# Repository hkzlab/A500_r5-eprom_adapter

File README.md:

# A500/A2000 EPROM Adapter

## Introduction

In this repository You'll find two no-frills boards that I designed with a simple problem to solve: allow me to install **multiple Kickstarts** in my Amiga 500 rev.5 units without having to shell out money for an expensive 27C400 that I then need to rewire to make compatible.

The board includes sockets for pullup resistors that are oftentimes required (if your Amiga doesn't already have them) when fitting an new EPROM.

The board accepts **two** 27C020/040/080 EPROMs programmed with concatenated Kickstart images.

## EPROMs Configuration

The Amiga 500 uses a 16-bit bus to access the Kickstart, as such, the original ROM and its replacements must be 16-bit memories: expensive and annoying to program.

This board merges the data path of two 8-bit EPROMs (cheaper, easier to program) to rebuild the 16-bit data path.

One must take care to divide the original Kickstart dumps in two halves by separating the most significant byte of each Word into a file, and the least significant into another.

See the following example. The following is a partial hex dump of Kickstart 1.3 for A500:

Once we split its words in High and Low bytes we'll get the following dump for the High part:

And the following for the Low part:

The **High** part will have to be inserted in the slot marked as **H** and the **Low** part in the slot marked as **L**.

You can use the [srecord](http://srecord.sourceforge.net/) tool to split the files:

```sh
srec_cat -o LOW.bin -binary fullrom.bin -binary -split 2 0
srec_cat -o HIGH.bin -binary fullrom.bin -binary -split 2 1

```

### A500 rev.5 configuration

The Amiga 500 rev.5 uses a non-standard pinout in its Kickstart socket: A17 line is connected to PIN 31, while it is normally on PIN 1 of the ROM chip.

You can wire the adapter to use this pinout by **bridging pins 2-3 of the J4 header**. If pins 1-2 are bridged, the A17 line goes to PIN 1.

### EPROM slots

Depending on which type of EPROM you use, you can fit a different number of Kickstart images in them.

- 27C020: 1 kickstart slot
- 27C040: 2 kickstarts slots (selectable with the A18 jumper)
- 27C080: 4 kickstarts slot (selectable by combining the A18 and A19 jumpers)

A18 and A19 are pulled-up through 4.7k resistors.

Every slot can host a 512kb Kickstart. If you wish to put a 256kb Kickstart in the slot, concatenate it with a copy of itself (stay on the safe side!).

To create an image to burn on the EPROMs I suggest following this procedure:

1. Take the required Kickstarts
2. Double the size of every 256kb Kickstart by concatenating it with a copy of itself
3. Concatenate the desired Kickstart dumps
4. Split the resulting binary file in high and low halves
5. Burn the halves to their respective EPROMs

The result will be like this for a 27C040:

```text
              HIGH EPROM     LOW  EPROM
         / .--------------.--------------.
        |  | 256k Kick A  | 256k Kick A  |
SLOT 1 <   +--------------+--------------+
        |  | 256k Kick A  | 256k Kick A  |
         \ +--------------+--------------+
         / |              |              |
        |  |     512k     |     512k     |
SLOT 2 <   |    Kick B    |    Kick B    |
        |  |              |              |
         \ '--------------'--------------'
```

## Board Variants

You'll find two variants of the same board in this repository. One uses DIP32 EPROMs, the other PLCC32.

PLCC32 version is a bit harder to solder, but is more compact.

**Install RN1 and RN2 only if your Amiga lacks pull-up resistors on the data lines**. Also, the **R1 and R2 resistors are to be installed ONLY if you fit a 9-resistor bussed network (so, 10 pin and not 11) or if you did not fit a resistor network at all** on RN1 and RN2. 11 pin bussed arrays are a bit hard to come by, so you can fit a 10 pin one and install two discrete resistors to make up for the missing ones.

### DIP32 Variant

#### BOM

- C1, C2: 100nF ceramic capacitors
- J2, J3: 1x2 2.54mm PCB headers
- J4: 1x3 2.54mm PCB header
- U2, U3: DIP32 sockets
- U1: install 2x20pin 2.54mm headers on the underside. **Find thin ones that can fit into sockets**.
- RN1, RN2: either 11 or 10pin 4.7k ohm bussed resistor networks.
  - If you fit a 10pin ones (9 resistor + common pin), leave the last pin empty and fit R1 and R2.
  - If you fit 11pin ones (10 resistors + common pin), leave R1 and R2 empty
- R1, R2: 4.7k ohm resistors. Read point above to see if you must install them or not.
- 2x 27C020/040/080 EPROMs, DIP32

### SMD PLCC32 variant

#### BOM

- C1, C2: 100nF ceramic capacitors
- J2, J3: 1x2 2.54mm PCB headers
- J4: 1x3 2.54mm PCB header
- U2, U3: PLCC32 SMD sockets
- U1: install 2x20pin 2.54mm headers on the underside. **Find thin ones that can fit into sockets**.
- RN1, RN2: either 11 or 10pin 4.7k ohm bussed resistor networks.
  - If you fit a 10pin ones (9 resistor + common pin), leave the last pin empty and fit R1 and R2.
  - If you fit 11pin ones (10 resistors + common pin), leave R1 and R2 empty
- R1, R2: 4.7k ohm resistors. Read point above to see if you must install them or not.
- 2x 27C020/040/080 EPROMs, DIP32

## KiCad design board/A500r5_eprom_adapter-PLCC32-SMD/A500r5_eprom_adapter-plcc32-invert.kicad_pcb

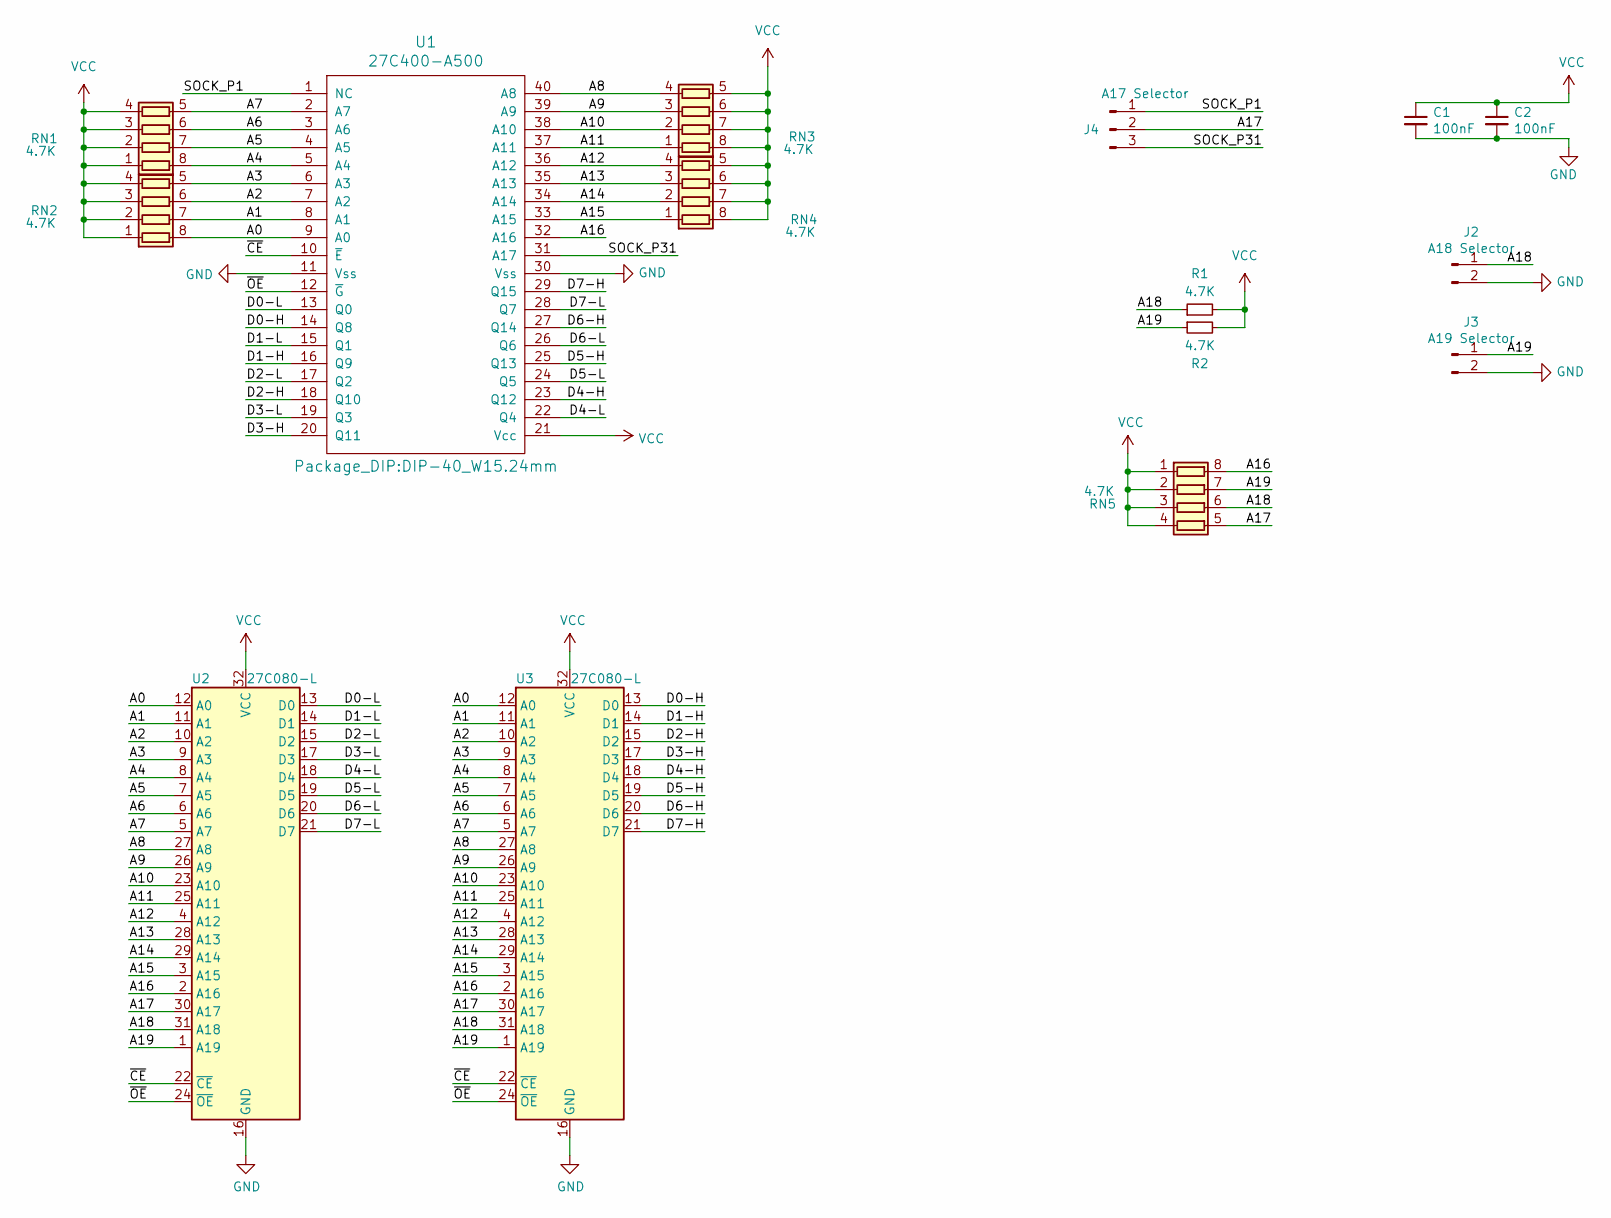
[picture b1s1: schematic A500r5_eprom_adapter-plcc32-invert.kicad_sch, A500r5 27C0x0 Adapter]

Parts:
C1, C2: 100nF; C_0603_1608Metric_Pad1.08x0.95mm_HandSolder
J2: A18 Selector; SolderJumper-2_P1.3mm_Open_RoundedPad1.0x1.5mm
J3: A19 Selector; SolderJumper-2_P1.3mm_Open_RoundedPad1.0x1.5mm
J4: A17 Selector; SolderJumper-3_P1.3mm_Open_RoundedPad1.0x1.5mm
R1, R2: 4.7K; R_0603_1608Metric_Pad0.98x0.95mm_HandSolder
RN1, RN2, RN3, RN4, RN5: 4.7K; R_Array_Convex_4x0612
U1: 27C400-A500; DIP-40_W15.24mm
U2, U3: 27C080-L; PLCC-32_11.4x14.0mm_P1.27mm

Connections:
/A0: RN2.8 (R1.2), U1.9 (A0), U2.12 (A0), U3.12 (A0)
/A1: RN2.7 (R2.2), U1.8 (A1), U2.11 (A1), U3.11 (A1)
/A2: RN2.6 (R3.2), U1.7 (A2), U2.10 (A2), U3.10 (A2)
/A3: RN2.5 (R4.2), U1.6 (A3), U2.9 (A3), U3.9 (A3)
/A4: RN1.8 (R1.2), U1.5 (A4), U2.8 (A4), U3.8 (A4)
/A5: RN1.7 (R2.2), U1.4 (A5), U2.7 (A5), U3.7 (A5)
/A6: RN1.6 (R3.2), U1.3 (A6), U2.6 (A6), U3.6 (A6)
/A7: RN1.5 (R4.2), U1.2 (A7), U2.5 (A7), U3.5 (A7)
/A8: RN3.4 (R4.1), U1.40 (A8), U2.27 (A8), U3.27 (A8)
/A9: RN3.3 (R3.1), U1.39 (A9), U2.26 (A9), U3.26 (A9)
/A10: RN3.2 (R2.1), U1.38 (A10), U2.23 (A10), U3.23 (A10)
/A11: RN3.1 (R1.1), U1.37 (A11), U2.25 (A11), U3.25 (A11)
/A12: RN4.4 (R4.1), U1.36 (A12), U2.4 (A12), U3.4 (A12)
/A13: RN4.3 (R3.1), U1.35 (A13), U2.28 (A13), U3.28 (A13)
/A14: RN4.2 (R2.1), U1.34 (A14), U2.29 (A14), U3.29 (A14)
/A15: RN4.1 (R1.1), U1.33 (A15), U2.3 (A15), U3.3 (A15)
/A16: RN5.8 (R1.2), U1.32 (A16), U2.2 (A16), U3.2 (A16)
/A17: J4.2, RN5.5 (R4.2), U2.30 (A17), U3.30 (A17)
/A18: J2.1, R1.1, RN5.6 (R3.2), U2.31 (A18), U3.31 (A18)
/A19: J3.1, R2.1, RN5.7 (R2.2), U2.1 (A19), U3.1 (A19)
/D0-H: U1.14 (Q8), U3.13 (D0)
/D0-L: U1.13 (Q0), U2.13 (D0)
/D1-H: U1.16 (Q9), U3.14 (D1)
/D1-L: U1.15 (Q1), U2.14 (D1)
/D2-H: U1.18 (Q10), U3.15 (D2)
/D2-L: U1.17 (Q2), U2.15 (D2)
/D3-H: U1.20 (Q11), U3.17 (D3)
/D3-L: U1.19 (Q3), U2.17 (D3)
/D4-H: U1.23 (Q12), U3.18 (D4)
/D4-L: U1.22 (Q4), U2.18 (D4)
/D5-H: U1.25 (Q13), U3.19 (D5)
/D5-L: U1.24 (Q5), U2.19 (D5)
/D6-H: U1.27 (Q14), U3.20 (D6)
/D6-L: U1.26 (Q6), U2.20 (D6)
/D7-H: U1.29 (Q15), U3.21 (D7)
/D7-L: U1.28 (Q7), U2.21 (D7)
/SOCK_P1: J4.1, U1.1 (NC)
/SOCK_P31: J4.3, U1.31 (A17)
/~CE: U1.10 (~E), U2.22 (~CE), U3.22 (~CE)
/~OE: U1.12 (~G), U2.24 (~OE), U3.24 (~OE)
GND: C1.2, C2.2, J2.2, J3.2, U1.11 (Vss), U1.30 (Vss), U2.16 (GND), U3.16 (GND)
VCC: C1.1, C2.1, R1.2, R2.2, RN1.1 (R1.1), RN1.2 (R2.1), RN1.3 (R3.1), RN1.4 (R4.1), RN2.1 (R1.1), RN2.2 (R2.1), RN2.3 (R3.1), RN2.4 (R4.1), RN3.5 (R4.2), RN3.6 (R3.2), RN3.7 (R2.2), RN3.8 (R1.2), RN4.5 (R4.2), RN4.6 (R3.2), RN4.7 (R2.2), RN4.8 (R1.2), RN5.1 (R1.1), RN5.2 (R2.1), RN5.3 (R3.1), RN5.4 (R4.1), U1.21 (Vcc), U2.32 (VCC), U3.32 (VCC)

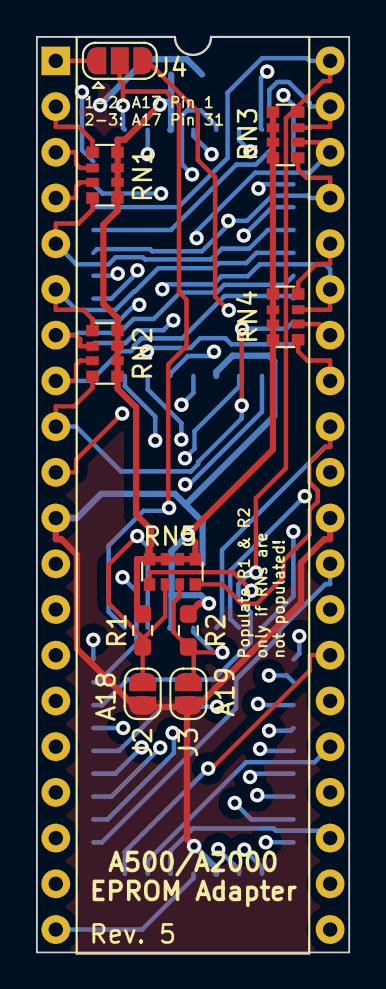
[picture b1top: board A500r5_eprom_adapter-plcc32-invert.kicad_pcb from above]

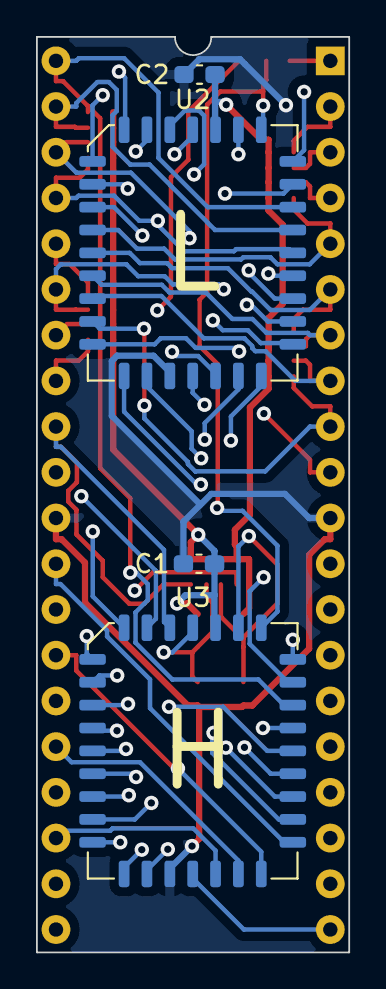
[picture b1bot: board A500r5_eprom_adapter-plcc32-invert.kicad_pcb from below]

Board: 4 copper layers, 17.4 x 50.9 mm, 15 parts (4 on the bottom side), 42 nets.

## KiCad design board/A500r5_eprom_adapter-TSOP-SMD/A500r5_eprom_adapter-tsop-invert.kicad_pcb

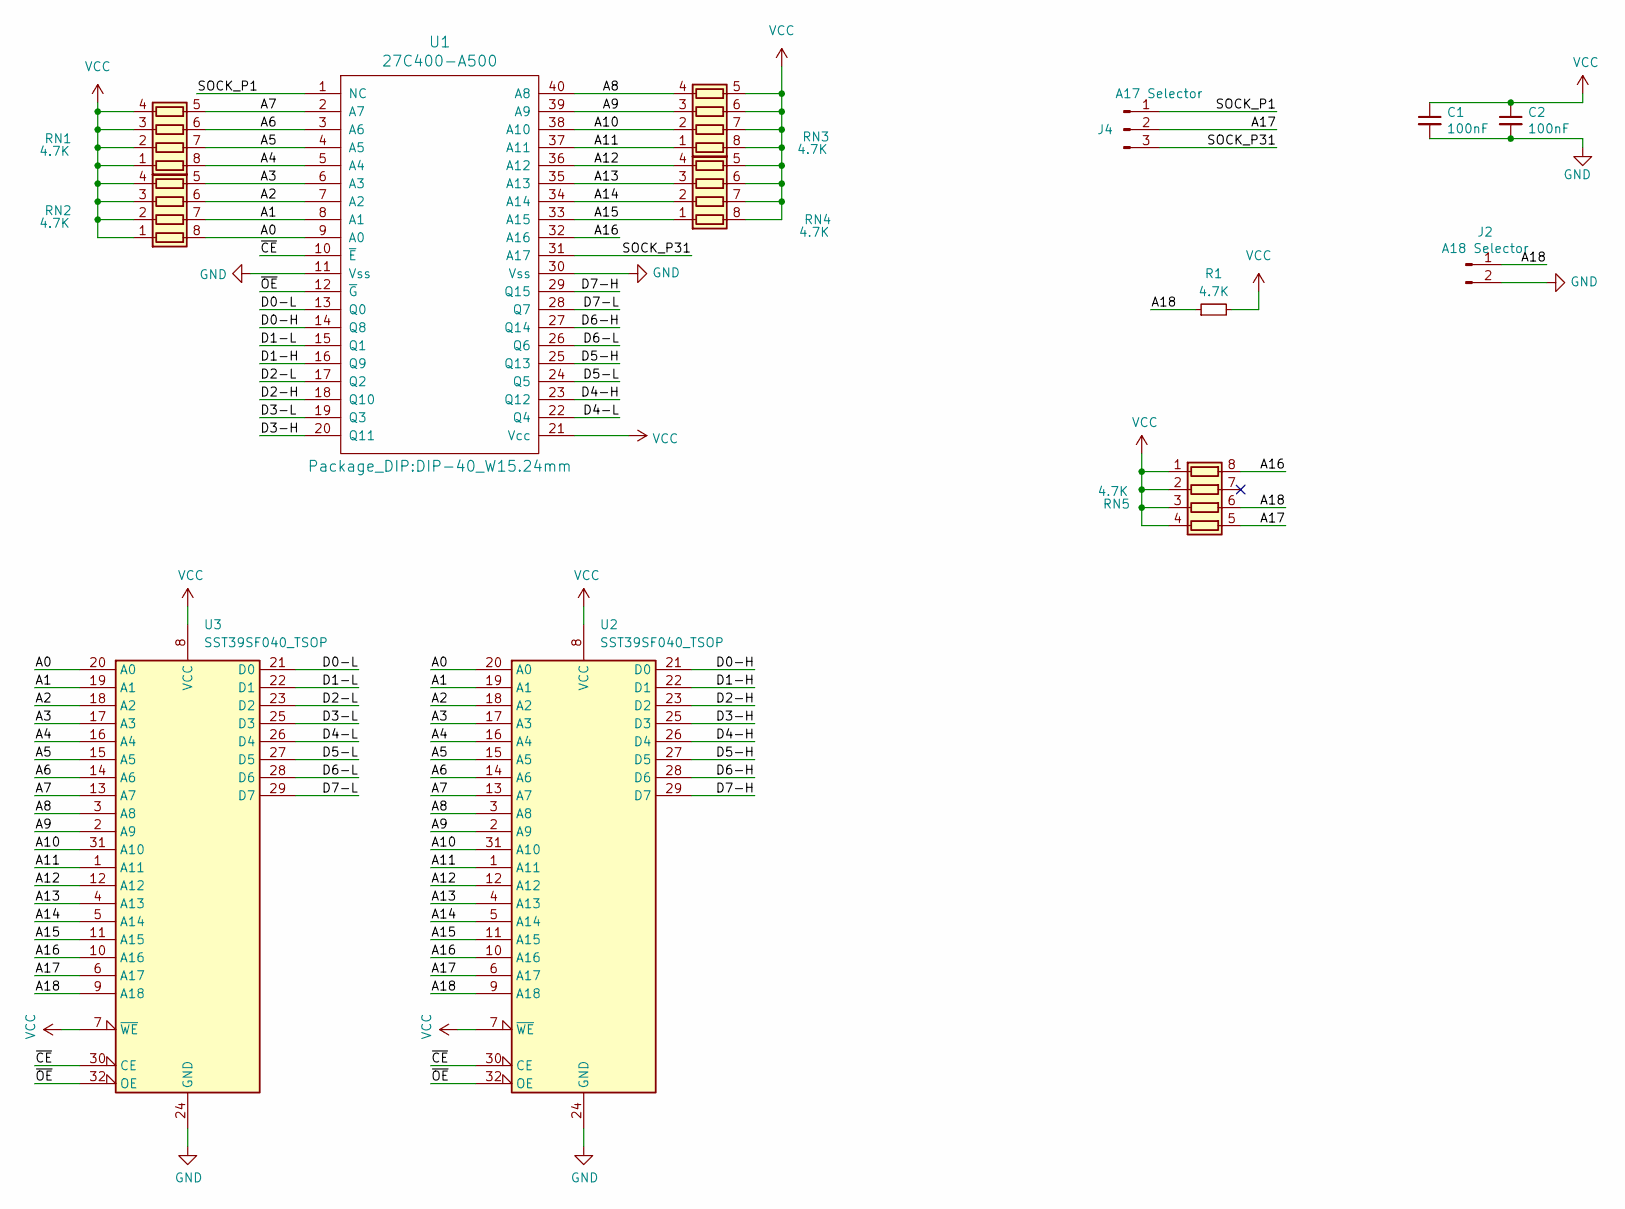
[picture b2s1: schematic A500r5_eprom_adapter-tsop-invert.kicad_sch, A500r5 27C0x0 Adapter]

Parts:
C1, C2: 100nF; C_0603_1608Metric_Pad1.08x0.95mm_HandSolder
J2: A18 Selector; SolderJumper-2_P1.3mm_Open_RoundedPad1.0x1.5mm
J4: A17 Selector; SolderJumper-3_P1.3mm_Open_RoundedPad1.0x1.5mm
R1: 4.7K; R_0603_1608Metric_Pad0.98x0.95mm_HandSolder
RN1, RN2, RN3, RN4, RN5: 4.7K; R_Array_Convex_4x0612
U1: 27C400-A500; DIP-40_W15.24mm
U2, U3: SST39SF040_TSOP; TSOP-I-32_14.4x8mm_P0.5mm

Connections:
/A0: RN2.8 (R1.2), U1.9 (A0), U2.20 (A0), U3.20 (A0)
/A1: RN2.7 (R2.2), U1.8 (A1), U2.19 (A1), U3.19 (A1)
/A2: RN2.6 (R3.2), U1.7 (A2), U2.18 (A2), U3.18 (A2)
/A3: RN2.5 (R4.2), U1.6 (A3), U2.17 (A3), U3.17 (A3)
/A4: RN1.8 (R1.2), U1.5 (A4), U2.16 (A4), U3.16 (A4)
/A5: RN1.7 (R2.2), U1.4 (A5), U2.15 (A5), U3.15 (A5)
/A6: RN1.6 (R3.2), U1.3 (A6), U2.14 (A6), U3.14 (A6)
/A7: RN1.5 (R4.2), U1.2 (A7), U2.13 (A7), U3.13 (A7)
/A8: RN3.4 (R4.1), U1.40 (A8), U2.3 (A8), U3.3 (A8)
/A9: RN3.3 (R3.1), U1.39 (A9), U2.2 (A9), U3.2 (A9)
/A10: RN3.2 (R2.1), U1.38 (A10), U2.31 (A10), U3.31 (A10)
/A11: RN3.1 (R1.1), U1.37 (A11), U2.1 (A11), U3.1 (A11)
/A12: RN4.4 (R4.1), U1.36 (A12), U2.12 (A12), U3.12 (A12)
/A13: RN4.3 (R3.1), U1.35 (A13), U2.4 (A13), U3.4 (A13)
/A14: RN4.2 (R2.1), U1.34 (A14), U2.5 (A14), U3.5 (A14)
/A15: RN4.1 (R1.1), U1.33 (A15), U2.11 (A15), U3.11 (A15)
/A16: RN5.8 (R1.2), U1.32 (A16), U2.10 (A16), U3.10 (A16)
/A17: J4.2, RN5.5 (R4.2), U2.6 (A17), U3.6 (A17)
/A18: J2.1, R1.1, RN5.6 (R3.2), U2.9 (A18), U3.9 (A18)
/D0-H: U1.14 (Q8), U2.21 (D0)
/D0-L: U1.13 (Q0), U3.21 (D0)
/D1-H: U1.16 (Q9), U2.22 (D1)
/D1-L: U1.15 (Q1), U3.22 (D1)
/D2-H: U1.18 (Q10), U2.23 (D2)
/D2-L: U1.17 (Q2), U3.23 (D2)
/D3-H: U1.20 (Q11), U2.25 (D3)
/D3-L: U1.19 (Q3), U3.25 (D3)
/D4-H: U1.23 (Q12), U2.26 (D4)
/D4-L: U1.22 (Q4), U3.26 (D4)
/D5-H: U1.25 (Q13), U2.27 (D5)
/D5-L: U1.24 (Q5), U3.27 (D5)
/D6-H: U1.27 (Q14), U2.28 (D6)
/D6-L: U1.26 (Q6), U3.28 (D6)
/D7-H: U1.29 (Q15), U2.29 (D7)
/D7-L: U1.28 (Q7), U3.29 (D7)
/SOCK_P1: J4.1, U1.1 (NC)
/SOCK_P31: J4.3, U1.31 (A17)
/~CE: U1.10 (~E), U2.30 (CE), U3.30 (CE)
/~OE: U1.12 (~G), U2.32 (OE), U3.32 (OE)
GND: C1.2, C2.2, J2.2, U1.11 (Vss), U1.30 (Vss), U2.24 (GND), U3.24 (GND)
VCC: C1.1, C2.1, R1.2, RN1.1 (R1.1), RN1.2 (R2.1), RN1.3 (R3.1), RN1.4 (R4.1), RN2.1 (R1.1), RN2.2 (R2.1), RN2.3 (R3.1), RN2.4 (R4.1), RN3.5 (R4.2), RN3.6 (R3.2), RN3.7 (R2.2), RN3.8 (R1.2), RN4.5 (R4.2), RN4.6 (R3.2), RN4.7 (R2.2), RN4.8 (R1.2), RN5.1 (R1.1), RN5.2 (R2.1), RN5.3 (R3.1), RN5.4 (R4.1), U1.21 (Vcc), U2.7 (~WE), U2.8 (VCC), U3.7 (~WE), U3.8 (VCC)

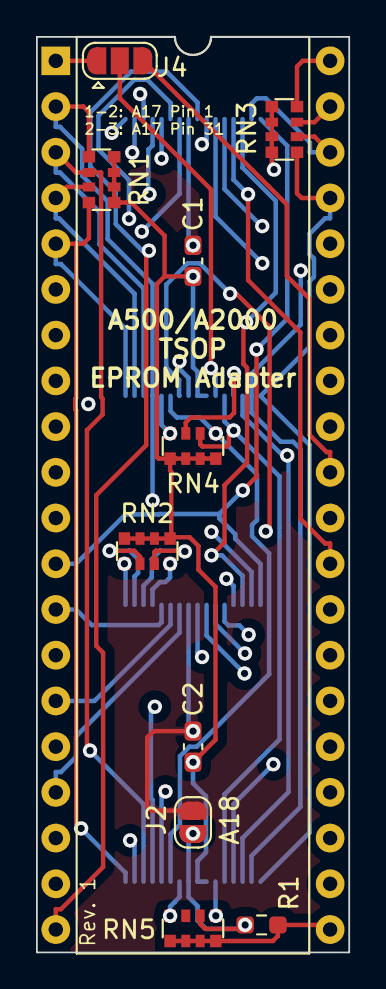
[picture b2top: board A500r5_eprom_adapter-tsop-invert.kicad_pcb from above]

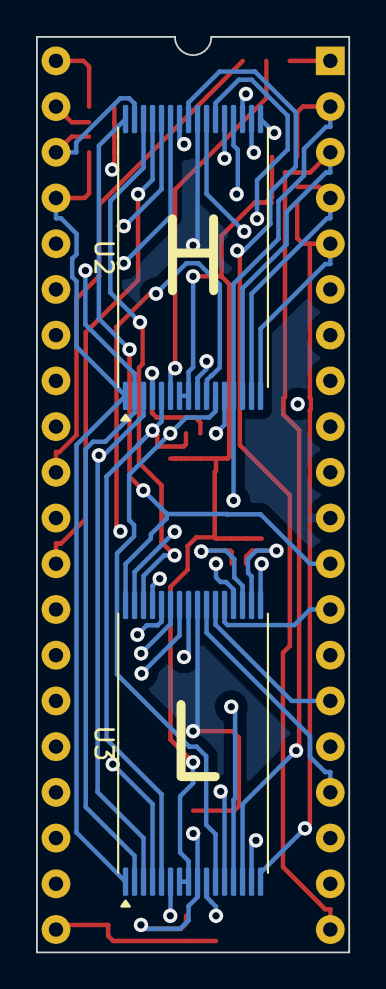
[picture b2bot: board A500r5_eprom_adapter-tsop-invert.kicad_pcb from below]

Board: 4 copper layers, 17.4 x 50.9 mm, 13 parts (2 on the bottom side), 41 nets.

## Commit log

2020-01-21 Add dataheets for ROMs to convert
2020-01-21 Add 27c040
2020-01-22 Add more components
2020-01-22 Complete the schematics
2020-01-22 Draw more of the PCB
2020-01-22 Changed to eeprom adapter
2020-01-23 More changes to the circuit
2020-01-23 Complete drawing of eprom adapter
2020-01-23 More changes
2020-01-24 Add beginning of PLCC32 version
2020-01-24 More PLCC32 changes
2020-01-24 Add more PLCC32 tracks
2020-01-24 More tracks
2020-01-25 Add changes and add gerbers
2020-01-25 Add gerbers
2020-01-25 Add more board variants
2020-01-25 More gerbers
2020-01-25 Deleted failed attempts
2020-01-25 Fix silkscreen
2020-02-28 add rev 1 for DIP adapter
2020-02-28 Update the SMD variant
2020-03-07 Restructure project
2020-08-17 Add preview pics and fixed gerbers
2020-08-17 Add README and licence
2020-08-18 Add A17 pin selector
2020-08-18 Draw rev.2 DIP PCB
2020-08-18 Add rev.2 boards
2020-08-18 Update file
2020-08-18 Cleanup silkscreen of PLCC32 version
2020-08-19 Add note on REV.2
2021-09-13 Updated notes on readme
2021-09-16 Updated PCB, getting ready for rev 3 of PLCC version, updated readme
2021-11-09 Removed kicad-pcb link
2024-09-10 Create an SMD rev 4
2024-09-10 Add schematics
2024-09-18 Update the PLCC adapter
2024-09-27 Add tsop adapter, untested
2024-09-29 Update the README
2025-01-18 Fix "A2000" silkscreen in PLCC and TSOP adapter variants
